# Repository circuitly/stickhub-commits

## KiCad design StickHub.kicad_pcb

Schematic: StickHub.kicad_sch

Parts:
C1: 1uF 10V; 1608_C; Voltage 16V; Tolerance 10%; MPN FS15B105K100PKG
C2: 0.1uF; 1608_C; Voltage 16V; Tolerance 10%; MPN CC0402KRX7R7BB104
C3, C4: 10uF 6.3V; 1608_C; Voltage 16V; Tolerance 10%; MPN CL05A106MQ5NUNC
C14, C15, C16, C17, C18, C19, C20, C21: 0.1uF 100V; 1608_C; Voltage 16V; Tolerance 10%; MPN NM0805B104K101CEDN
C22, C23, C24, C25, C26, C27, C29, C30, C31, C32, C33, C34, C35, C36, C37: 22uF 10V; 1608_C; Voltage 16V; Tolerance 10%; MPN GRM188R61A226ME15D
C38: 330uF 10V; CP_Elec_6.3x7.7
D1, D2, D3, D4, D5, D6, D7, D8, D9, D10, D11, D12, D13, D14, D22, D23: TVS; 1006_C; MPN AR0521P1
D15, D16, D17, D18, D19, D20, D21: USB; Duo_LED_1.6x0.8_Kingbright_APHB1608LZGKSURKC; MPN APHB1608SGEC
D24, D25: 5V; 1006_C; MPN D5V0H1B2LP-7B
H1: Strap; Plain_Hole_3mm
J1: HOST; USB_A_PCB_traces_small
J2: USB1; JST_SH_SM04B-SRSS-TB_1x04-1MP_P1.00mm_Horizontal; MPN SM04B-SRSS-TB(LF)(SN)
J3: USB2; JST_SH_SM04B-SRSS-TB_1x04-1MP_P1.00mm_Horizontal; MPN SM04B-SRSS-TB(LF)(SN)
J4: USB3; JST_SH_SM04B-SRSS-TB_1x04-1MP_P1.00mm_Horizontal; MPN SM04B-SRSS-TB(LF)(SN)
J5: USB4; JST_SH_SM04B-SRSS-TB_1x04-1MP_P1.00mm_Horizontal; MPN SM04B-SRSS-TB(LF)(SN)
J6: USB5; JST_SH_SM04B-SRSS-TB_1x04-1MP_P1.00mm_Horizontal; MPN SM04B-SRSS-TB(LF)(SN)
J7: USB6; JST_SH_SM04B-SRSS-TB_1x04-1MP_P1.00mm_Horizontal; MPN SM04B-SRSS-TB(LF)(SN)
J8: USB7; JST_SH_SM04B-SRSS-TB_1x04-1MP_P1.00mm_Horizontal; MPN SM04B-SRSS-TB(LF)(SN)
J9: EXTGND; 1P-1.5x1.5
JP1: EXTPWR; PinHeader_1x02_P2.54mm_Vertical
LOGO1, LOGO2, LOGO3, LOGO4: Logo
R1: 10k; 1608_C; MPN 0402WGF1002TCE
R2, R3, R4, R5: 100k; 1608_C; MPN 0402WGF1003TCE
R6: 2.7k; 1608_C; MPN 0402WGF2701TCE
R7, R8, R9, R10, R11, R12, R13: 470; 1608_C; MPN 0402WGF4700TCE
U1: MaxLinear_XR22417-48; LQFP-48_7x7mm_P0.5mm; MPN XR22417CV48TR-F
Y1: 12MHz 50ppm 16-20pF; Crystal_4-SMD_2.5x2mm; MPN CM4012M00020T8188026

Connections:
+1V8: C4.1, U1.6 (VCC18), U1.21 (VCC18), U1.25 (1V8_OUT), U1.28 (VCC18)
+3.3V: C3.1, R3.1, R4.1, R5.1, U1.9 (3V3_OUT), U1.15 (VCC33), U1.20 (VCC33), U1.26 (VCC33), U1.31 (VCC33), U1.36 (VCC33), U1.42 (VCC33)
+5V: C1.1, C14.1, C15.1, C16.1, C17.1, C18.1, C19.1, C20.1, C22.1, C23.1, C24.1, C25.1, C26.1, C27.1, C29.1, C30.1, C31.1, C32.1, C33.1, C34.1, C35.1, C36.1, C37.1, C38.1 (+), D25.2 (A2), J2.1, J3.1, J4.1, J5.1, J6.1, J7.1, J8.1, R1.1, U1.8 (VCC5)
/D+: D23.2 (A2), J1.3, U1.30 (UP_D+)
/D-: D22.2 (A2), J1.2, U1.29 (UP_D-)
/LC: D15.GK (2), D15.RA (3), D16.GK (2), D16.RA (3), D17.GK (2), D17.RA (3), D18.GK (2), D18.RA (3), D19.GK (2), D19.RA (3), D20.GK (2), D20.RA (3), D21.GK (2), D21.RA (3), U1.1 (LED_CTL)
/LED1: R7.2, U1.3 (LED1/SCL)
/LED2: R8.2, U1.4 (LED2)
/LED3: R9.2, U1.5 (LED3)
/LED4: R10.2, U1.7 (LED4)
/LED5: R11.2, U1.48 (LED5)
/LED6: R12.2, U1.47 (LED6)
/LED7: R13.2, U1.46 (LED7)
/U1D+: D2.2 (A2), J2.3, U1.19 (USB1D+)
/U1D-: D1.2 (A2), J2.2, U1.18 (USB1D-)
/U2D+: D4.2 (A2), J3.3, U1.17 (USB2D+)
/U2D-: D3.2 (A2), J3.2, U1.16 (USB2D-)
/U3D+: D6.2 (A2), J4.3, U1.14 (USB3D+)
/U3D-: D5.2 (A2), J4.2, U1.13 (USB3D-)
/U4D+: D8.2 (A2), J5.3, U1.12 (USB4D+)
/U4D-: D7.2 (A2), J5.2, U1.11 (USB4D-)
/U5D+: D10.2 (A2), J6.3, U1.33 (USB5D+)
/U5D-: D9.2 (A2), J6.2, U1.32 (USB5D-)
/U6D+: D12.2 (A2), J7.3, U1.35 (USB6D+)
/U6D-: D11.2 (A2), J7.2, U1.34 (USB6D-)
/U7D+: D14.2 (A2), J8.3, U1.38 (USB7D+)
/U7D-: D13.2 (A2), J8.2, U1.37 (USB7D-)
/XI: U1.22 (XTALIN), Y1.1
/XO: U1.23 (XTALOUT), Y1.3
GND: C1.2, C2.2, C3.2, C4.2, C14.2, C15.2, C16.2, C17.2, C18.2, C19.2, C20.2, C21.2, C22.2, C23.2, C24.2, C25.2, C26.2, C27.2, C29.2, C30.2, C31.2, C32.2, C33.2, C34.2, C35.2, C36.2, C37.2, C38.2 (-), D1.1 (A1), D2.1 (A1), D3.1 (A1), D4.1 (A1), D5.1 (A1), D6.1 (A1), D7.1 (A1), D8.1 (A1), D9.1 (A1), D10.1 (A1), D11.1 (A1), D12.1 (A1), D13.1 (A1), D14.1 (A1), D22.1 (A1), D23.1 (A1), D24.1 (A1), D25.1 (A1), J1.4, J2.4, J2.MP (MountPin), J3.4, J3.MP (MountPin), J4.4, J4.MP (MountPin), J5.4, J5.MP (MountPin), J6.4, J6.MP (MountPin), J7.4, J7.MP (MountPin), J8.4, J8.MP (MountPin), J9.1, R2.2, R6.2, U1.10 (GND), U1.24 (GND), U1.39 (GND), Y1.2 (GND), Y1.4 (GND)
unnamed: D15.GA (1), D15.RK (4), R7.1
unnamed: D16.GA (1), D16.RK (4), R8.1
unnamed: D17.GA (1), D17.RK (4), R9.1
unnamed: D18.GA (1), D18.RK (4), R10.1
unnamed: D19.GA (1), D19.RK (4), R11.1
unnamed: D20.GA (1), D20.RK (4), R12.1
unnamed: D21.GA (1), D21.RK (4), R13.1
unnamed: J1.1, JP1.1
unnamed: R3.2, U1.40 (EXT_RST#)
unnamed: R6.1, U1.27 (REXT)
unnamed: R5.2, U1.43 (TEST1#)
unnamed: R4.2, U1.45 (TEST3#)
unnamed: C2.1, R1.2, R2.1, U1.41 (VBUS_SENSE)
VIN: C21.1, D24.2 (A2), JP1.2

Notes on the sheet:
ESD caps at connectors / plug
Shared VBUS capacitance

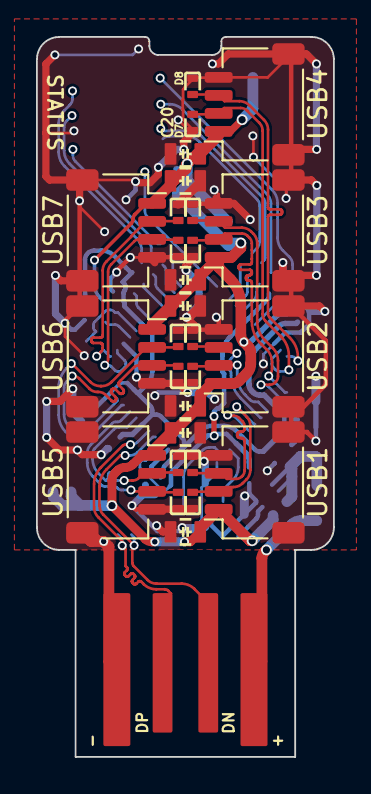
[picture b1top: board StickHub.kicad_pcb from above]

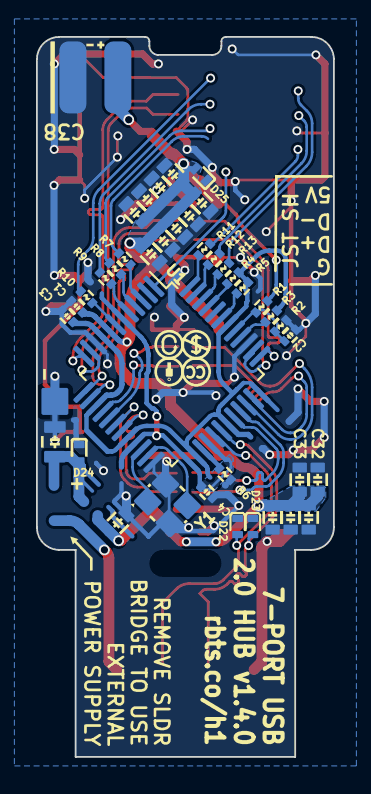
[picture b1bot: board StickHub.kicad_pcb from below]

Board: 2 copper layers, 16.5 x 40.0 mm, 75 parts (45 on the bottom side), 35 nets.

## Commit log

2024-06-05 Initial commit.
2024-06-05 Removing chunks of schematic and board.
2024-06-05 Revert "Removing chunks of schematic and board."
    This reverts commit 6f6bff356a7eff26be86b812d608cab446a31a50.
2024-06-05 Changing capacitor values.
